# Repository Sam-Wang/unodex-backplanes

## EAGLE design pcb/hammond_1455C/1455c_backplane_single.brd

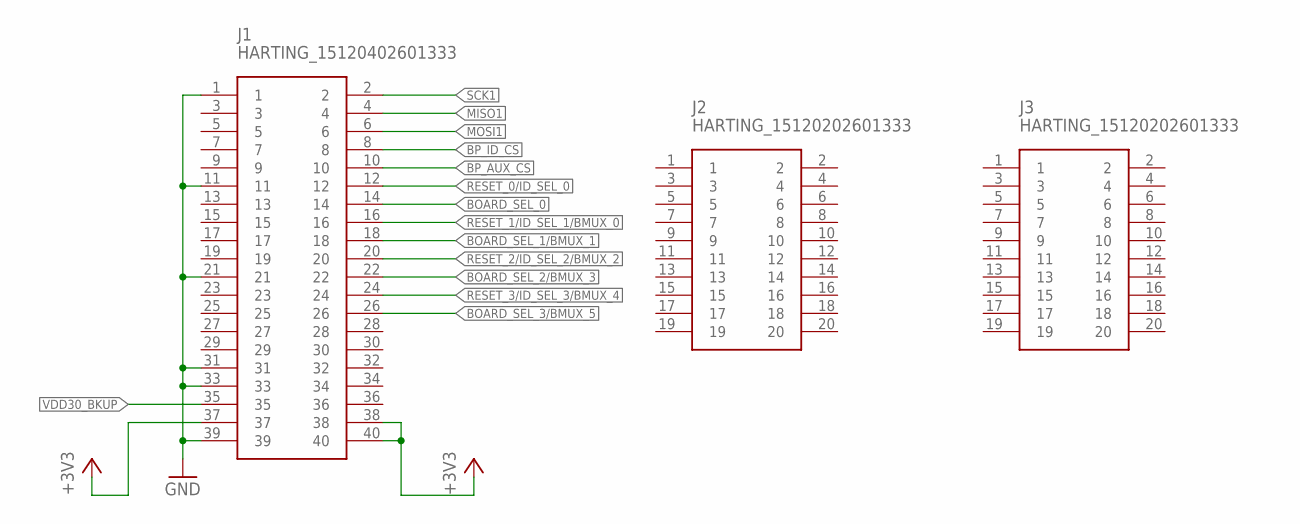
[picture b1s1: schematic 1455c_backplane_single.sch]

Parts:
J1: HARTING_15120402601333
J2, J3: HARTING_15120202601333

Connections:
+3V3: J1.37, J1.38, J1.40
BOARD_SEL_0: J1.14
BOARD_SEL_1/BMUX_1: J1.18
BOARD_SEL_2/BMUX_3: J1.22
BOARD_SEL_3/BMUX_5: J1.26
BP_AUX_CS: J1.10
BP_ID_CS: J1.8
GND: J1.1, J1.11, J1.21, J1.31, J1.33, J1.39
MISO1: J1.4
MOSI1: J1.6
RESET_0/ID_SEL_0: J1.12
RESET_1/ID_SEL_1/BMUX_0: J1.16
RESET_2/ID_SEL_2/BMUX_2: J1.20
RESET_3/ID_SEL_3/BMUX_4: J1.24
SCK1: J1.2
VDD30_BKUP: J1.35

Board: 2 copper layers, 3 parts (0 on the bottom side), 2 nets, no tracks yet.

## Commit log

2016-07-25 Add Hammond 54x23mm extruded enclosure backplane
2016-07-26 Add main board backplane connector drawings
